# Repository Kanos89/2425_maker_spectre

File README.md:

# 2425_maker_spectre

## Introduction

### Context

This project is made in the context of the second year option called "Maker" at the French graduate school ENSEA ([https://www.ensea.fr](https://www.ensea.fr)). This option encourages learning by doing, using several manufacturing tools as part of a personal project.

### My project

The idea is to build a drone from almost non-existent knowledge in this field (and so to learn how it's done). The drone will be a quadrotor and its theme will be the spectrum of the Destiny video game series (see photo below). The ultimate aim is to turn it into a companion that will follow its ‘master’ wherever he goes.

## -Project milestones

### -Creating a flight control PCB

### -Creating a light 3D body which represents the drone from the game

### -Creating a 4 in 1 ESC PCB

### -Learn how to implement/use Betaflight for the software part

### -Design and aesthetics

Build a drone inspired by the Spectrum companion from Destiny, keeping the design functional and yet recognizable.

- Use 3D CAD tools to make the drone's skeleton
- (Use of fabrics to lighten the body, maybe in future versions)
- The design shouldn't disrupt the functioning

### For later work - Implement autonomous navigation

Program the drone to follow a "master".

- Compare and decide which technology to use to implement this function by comparing many factors (need for computing power, ease of implementation, precision)

## Tools and Materials

### Tools

#### Software:

- CAD software:
  - We will learn and use Onshape for designing the frame
  - We will design our PCB on KiCAD
- Flight control software:
  - We will use Betaflight solutions

#### Hardware:

- 3D printer for the frame (PCB, motors, and battery support + design of the drone body)
- Fabrics for the design (flat surfaces)
- Soldering station for assembling components on the PCB

### Materials:

#### Actuator

- Brushless motors and propellers suitable for quadrotor drones

#### Control

- Flight controller
- ESC (Electronic Speed Controllers)
  - Designing one can be an objective, buying one is too easy :)

#### Energy

- Use of Lipo 2S for the drone

#### Sensors

- IMU = Accelerometer + Gyroscope
- Barometer for altitude
- For autonomous part (in further versions):
  - Bluetooth antenna (find target relative position)
  - ToF sensor (obstacle avoidance)

#### Communication

- Radio transmitter
- For autonomous part: Bluetooth

#### Frame

- Lightweight materials for the body:
  - PLA: find balance between solidity and weight
  - (Fabric instead of full printed faces)
  - 3D design of the drone with Onshape

- Work done from now on:
  - Flight control PCB with KiCad:

- Honorable mention for KiCad who only crashed 4 times during the rooting phase :)

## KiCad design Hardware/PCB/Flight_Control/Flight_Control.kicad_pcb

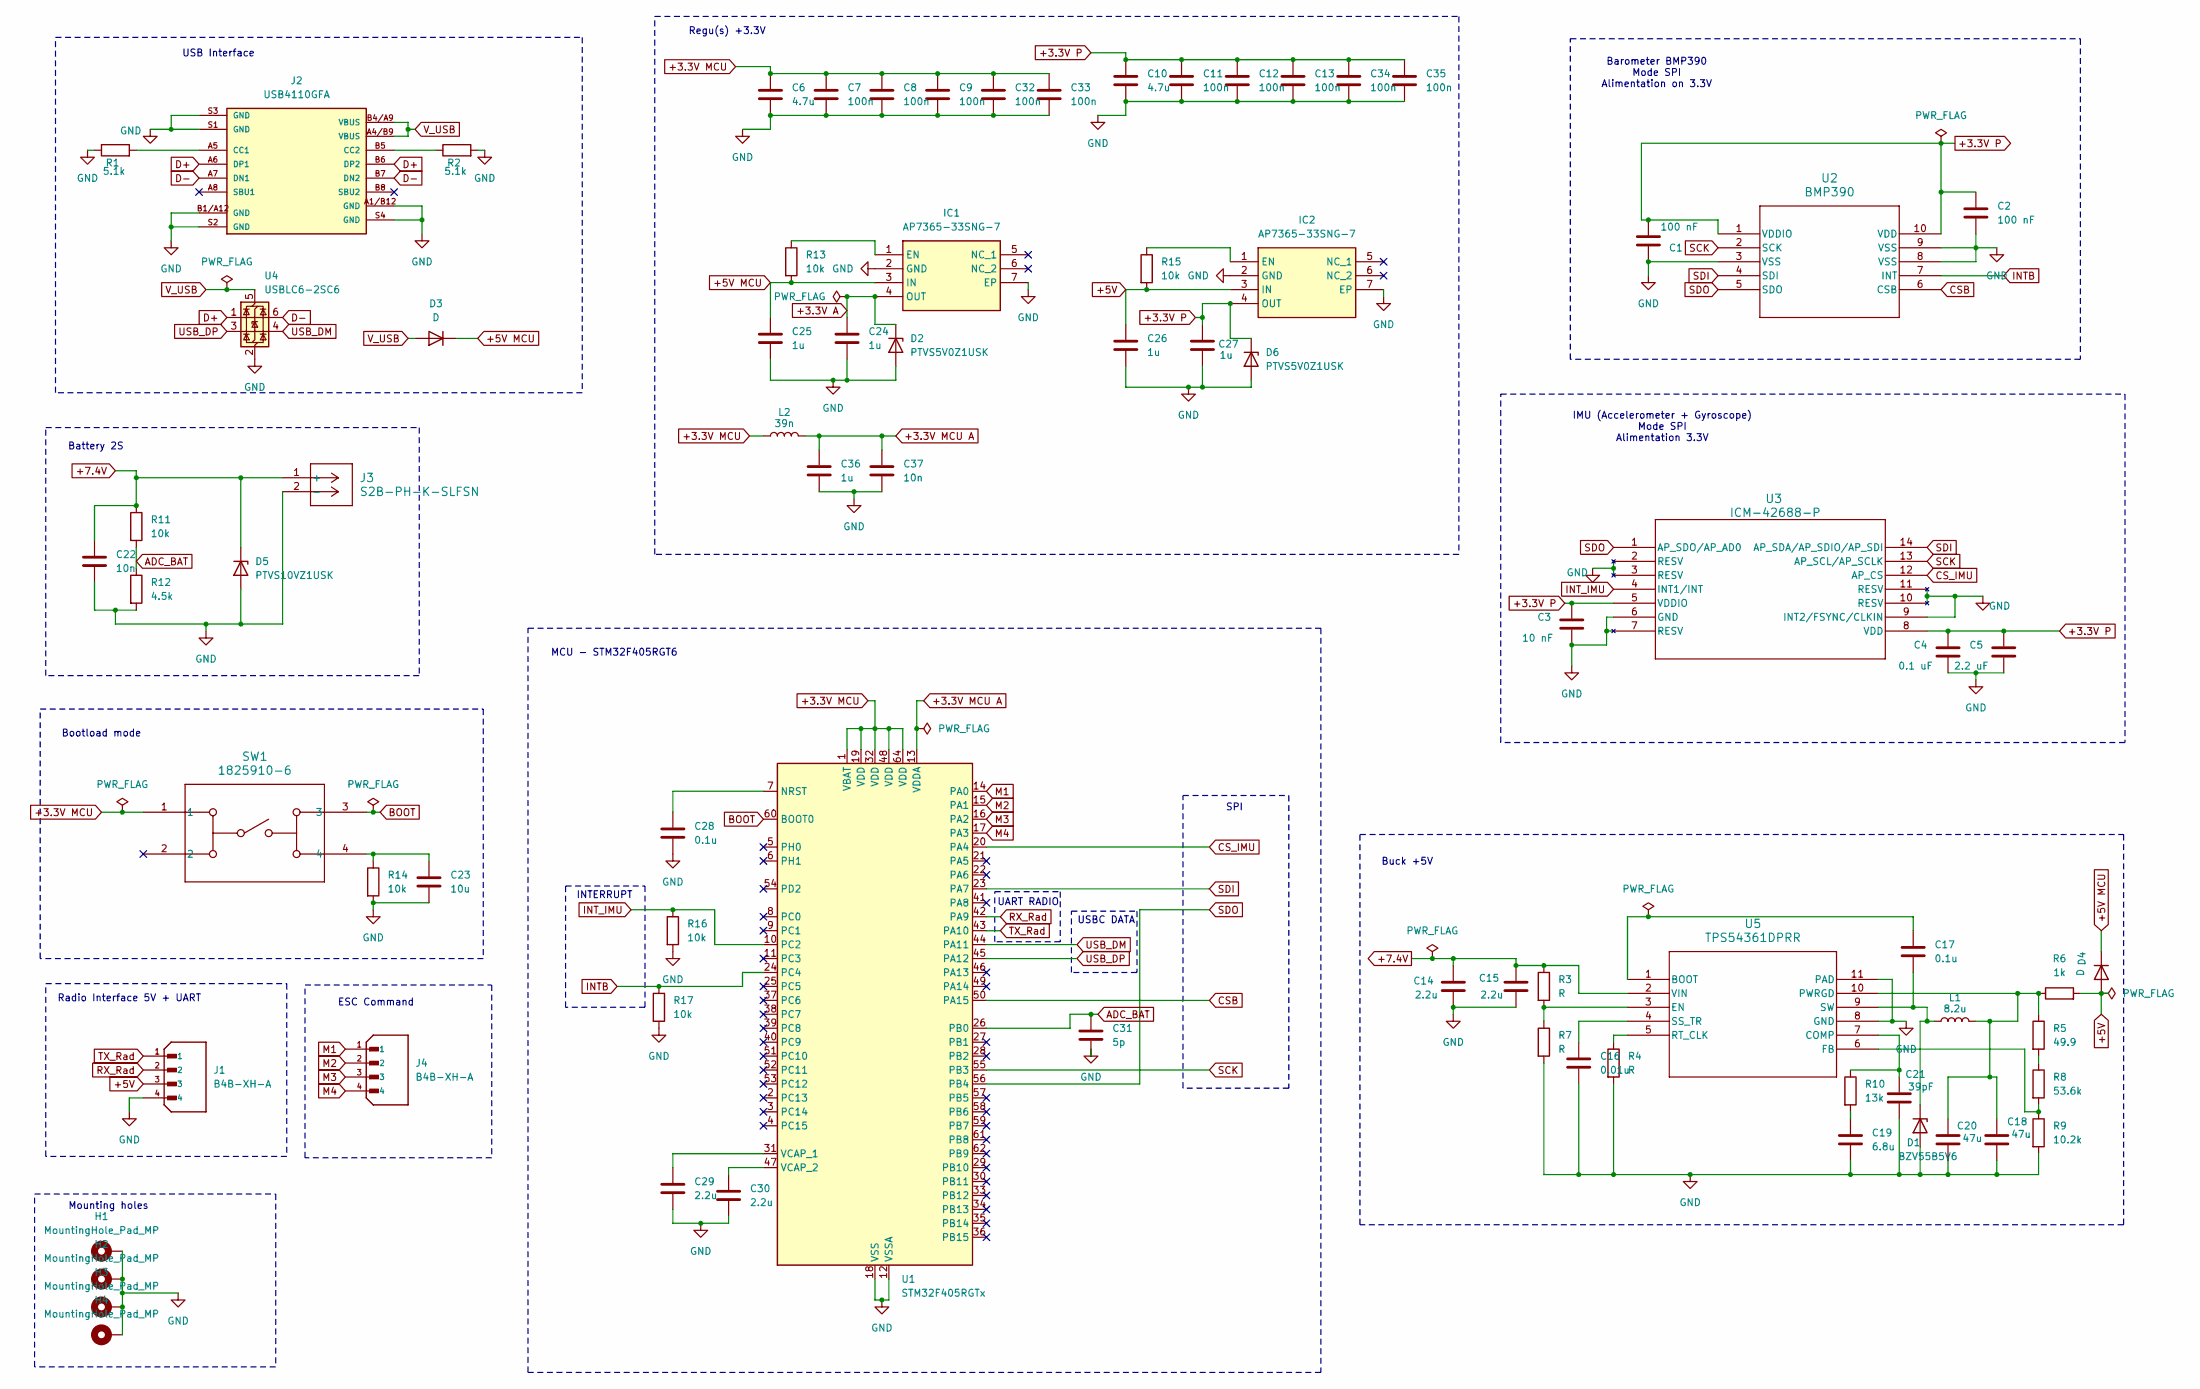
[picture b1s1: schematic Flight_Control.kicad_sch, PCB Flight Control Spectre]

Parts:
C1, C2: 100 nF; C_0402_1005Metric
C3: 10 nF; C_0402_1005Metric
C4: 0.1 uF; C_0402_1005Metric
C5: 2.2 uF; C_0402_1005Metric
C6, C10: 4.7u; C_0402_1005Metric
C7, C8, C9, C11, C12, C13, C32, C33, C34, C35: 100n; C_0402_1005Metric
C14, C15, C29, C30: 2.2u; C_0402_1005Metric
C16: 0.01u; C_0402_1005Metric
C17, C28: 0.1u; C_0402_1005Metric
C18, C20: 47u; C_0402_1005Metric
C19: 6.8u; C_0402_1005Metric
C21: 39pF; C_0402_1005Metric
C22, C37: 10n; C_0402_1005Metric
C23: 10u; C_0402_1005Metric
C24, C25, C26, C27, C36: 1u; C_0402_1005Metric
C31: 5p; C_0402_1005Metric
D1: BZV55B5V6; D_MiniMELF
D2, D6: PTVS5V0Z1USK; Nexperia_DSN1608-2_1.6x0.8mm
D3, D4: D; D_0402_1005Metric
D5: PTVS10VZ1USK; Nexperia_DSN1608-2_1.6x0.8mm
H1, H2, H3, H4: MountingHole_Pad_MP; MountingHole_2.2mm_M2
IC1, IC2: AP7365-33SNG-7; AP2301SN7; Mouser Part Number 621-AP7365-33SNG-7
J1, J4: B4B-XH-A; JST_B4B-XH-A
J2: USB4110GFA; GCT_USB4110GFA
J3: S2B-PH-K-SLFSN; CONN_S2B-PH-K-S_JST
L1: 8.2u; L_0402_1005Metric
L2: 39n; L_0402_1005Metric
R1, R2: 5.1k; R_0402_1005Metric
R3, R4, R7: R; R_0402_1005Metric
R5: 49.9; R_0402_1005Metric
R6: 1k; R_0402_1005Metric
R8: 53.6k; R_0402_1005Metric
R9: 10.2k; R_0402_1005Metric
R10: 13k; R_0402_1005Metric
R11, R13, R14, R15, R16, R17: 10k; R_0402_1005Metric
R12: 4.5k; R_0402_1005Metric
SW1: 1825910-6; SW4_1825910-B_TEC
U1: STM32F405RGTx; LQFP-64_10x10mm_P0.5mm
U2: BMP390
U3: ICM-42688-P; LGA14_2P5X3X0P91_TDK
U4: USBLC6-2SC6; SOT-23-6
U5: TPS54361DPRR; DPR0010A_TEX

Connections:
+3.3V A: C24.1, D2.1 (K), IC1.4 (OUT)
+3.3V MCU: C6.1, C7.1, C8.1, C9.1, C32.1, C33.1, L2.1, SW1.1, U1.1 (VBAT), U1.19 (VDD), U1.32 (VDD), U1.48 (VDD), U1.64 (VDD)
+3.3V MCU A: C36.1, C37.1, L2.2, U1.13 (VDDA)
+3.3V P: C1.2, C2.1, C3.1, C4.1, C5.1, C10.1, C11.1, C12.1, C13.1, C27.1, C34.1, C35.1, D6.1 (K), IC2.4 (OUT), U2.1 (VDDIO), U2.10 (VDD), U3.5 (VDDIO), U3.8 (VDD)
+5V: C26.1, D4.2 (A), IC2.3 (IN), J1.3, R6.2, R15.2
+5V MCU: C25.1, D3.1 (K), D4.1 (K), IC1.3 (IN), R13.2
+7.4V: C14.1, C15.1, C22.1, D5.1 (K), J3.1 (+), R3.1, R11.1, U5.2 (VIN)
ADC_BAT: C31.1, R11.2, R12.1, U1.26 (PB0)
BOOT: SW1.3, U1.60 (BOOT0)
CSB: U1.50 (PA15), U2.6 (CSB)
CS_IMU: U1.20 (PA4), U3.12 (AP_CS)
D+: J2.A6 (DP1), J2.B6 (DP2), U4.1 (I/O1)
D-: J2.A7 (DN1), J2.B7 (DN2), U4.6 (I/O1)
GND: C1.1, C2.2, C3.2, C4.2, C5.2, C6.2, C7.2, C8.2, C9.2, C10.2, C11.2, C12.2, C13.2, C14.2, C15.2, C16.2, C18.2, C19.2, C20.2, C21.2, C22.2, C23.2, C24.2, C25.2, C26.2, C27.2, C28.2, C29.2, C30.2, C31.2, C32.2, C33.2, C34.2, C35.2, C36.2, C37.2, D1.2 (A), D2.2 (A), D5.2 (A), D6.2 (A), H1.MP, H2.MP, H3.MP, H4.MP, IC1.2 (GND), IC1.7 (EP), IC2.2 (GND), IC2.7 (EP), J1.4, J2.A1/B12 (GND), J2.B1/A12 (GND), J2.S1 (GND), J2.S2 (GND), J2.S3 (GND), J2.S4 (GND), J3.2 (-), R1.1, R2.2, R4.2, R7.2, R9.2, R12.2, R14.2, R16.2, R17.2, U1.12 (VSSA), U1.18 (VSS), U1.63 (VSS), U2.3 (VSS), U2.8 (VSS), U2.9 (VSS), U3.2 (RESV), U3.3 (RESV), U3.6 (GND), U3.7 (RESV), U3.9 (INT2/FSYNC/CLKIN), U3.10 (RESV), U3.11 (RESV), U4.2 (GND), U5.8 (GND), U5.11 (PAD)
INTB: R17.1, U1.24 (PC4), U2.7 (INT)
INT_IMU: R16.1, U1.10 (PC2), U3.4 (INT1/INT)
M1: J4.1, U1.14 (PA0)
M2: J4.2, U1.15 (PA1)
M3: J4.3, U1.16 (PA2)
M4: J4.4, U1.17 (PA3)
unnamed: C19.1, R10.2
unnamed: C23.1, R14.1, SW1.4
unnamed: C17.2, D1.1 (K), L1.1, U5.9 (SW)
unnamed: IC1.1 (EN), R13.1
unnamed: IC2.1 (EN), R15.1
unnamed: J2.A5 (CC1), R1.2
unnamed: J2.B5 (CC2), R2.1
unnamed: R5.2, R8.1
unnamed: C28.1, U1.7 (NRST)
unnamed: C29.1, U1.31 (VCAP_1)
unnamed: C30.1, U1.47 (VCAP_2)
unnamed: C17.1, U5.1 (BOOT)
unnamed: C21.1, R10.1, U5.7 (COMP)
unnamed: R3.2, R7.1, U5.3 (EN)
unnamed: R8.2, R9.1, U5.6 (FB)
unnamed: C18.1, C20.1, L1.2, R5.1, R6.1, U5.10 (PWRGD)
unnamed: R4.1, U5.5 (RT_CLK)
unnamed: C16.1, U5.4 (SS_TR)
RX_Rad: J1.2, U1.42 (PA9)
SCK: U1.55 (PB3), U2.2 (SCK), U3.13 (AP_SCL/AP_SCLK)
SDI: U1.23 (PA7), U2.4 (SDI), U3.14 (AP_SDA/AP_SDIO/AP_SDI)
SDO: U1.56 (PB4), U2.5 (SDO), U3.1 (AP_SDO/AP_AD0)
TX_Rad: J1.1, U1.43 (PA10)
USB_DM: U1.44 (PA11), U4.4 (I/O2)
USB_DP: U1.45 (PA12), U4.3 (I/O2)
V_USB: D3.2 (A), J2.A4/B9 (VBUS), J2.B4/A9 (VBUS), U4.5 (VBUS)

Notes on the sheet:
Bootload mode
ESC Command
Barometer BMP390 Mode SPI Alimentation on 3.3V
Regu(s) +3.3V
IMU (Accelerometer + Gyroscope) Mode SPI Alimentation 3.3V
SPI
INTERRUPT
Battery 2S
MCU - STM32F405RGT6
Buck +5V
UART RADIO
USB Interface
USBC DATA
Mounting holes
Radio Interface 5V + UART

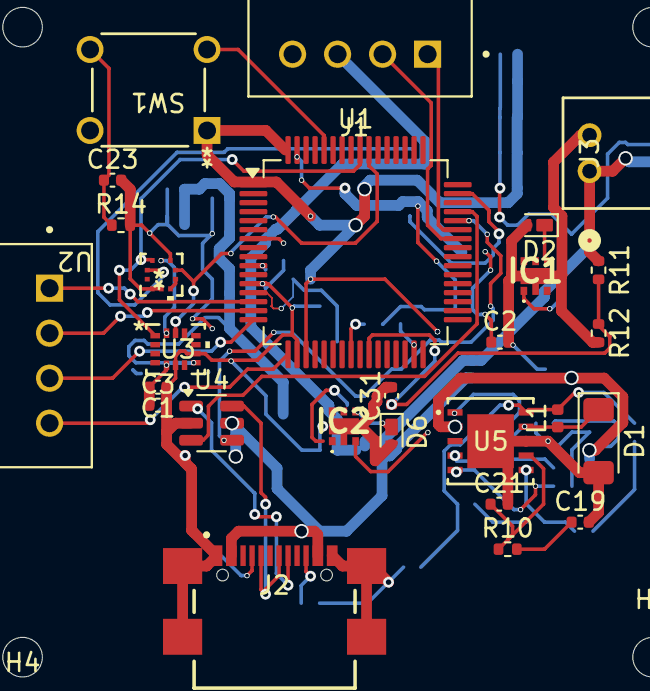
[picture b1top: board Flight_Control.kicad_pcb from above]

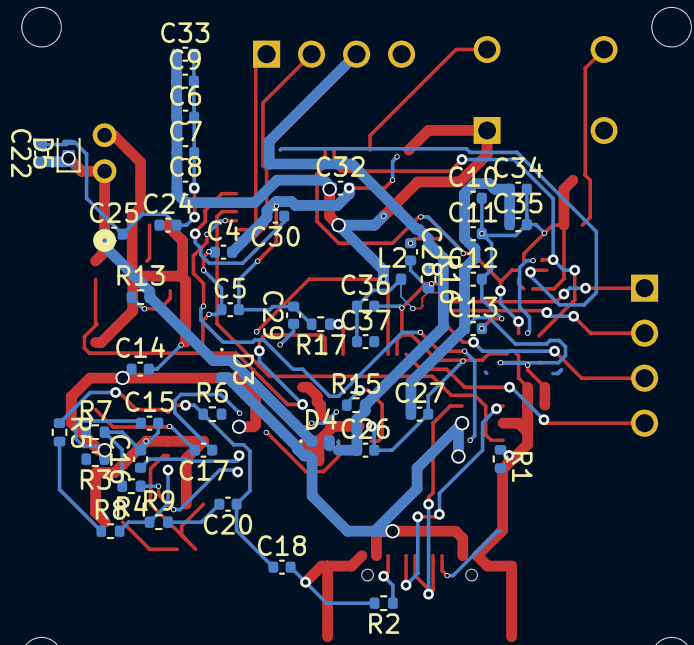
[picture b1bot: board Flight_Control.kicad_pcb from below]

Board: 4 copper layers, 78 parts (47 on the bottom side), 46 nets.

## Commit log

2025-01-20 Main struct of README.md
    Intro + Objectives + idead of Tools and material
2025-01-20 Update README.md
    add retro planning (temporary)
2025-01-20 Update README.md
    adapt the size of image in introduction (reduction)
2025-03-23 update_pcb + datasheet
2025-03-24 schematic_pcb
2025-03-24 pcb_root_unfinished
2025-04-27 update_pcb
2025-04-27 add 3D_model
